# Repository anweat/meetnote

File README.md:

# MeetNote · 可挂佩的 AI 会议助手

[中文](README.md) · [English](README.en.md) · [在线主页](https://anweat.github.io/meetnote/)

> 从「桌面会议记录器」到「圆润、可挂佩的 AI 助手」：四轮产品定义、硬件架构、结构/热设计与成本研究。

**状态：工程概念研究 · `BLOCKED / NOT FOR FAB`。**
本项目交付的是可编辑、可复核的设计研究资料，**不可投板、不可采购、不可作为量产或性能承诺**。所有功耗、续航、温度、成本均为设计估算，尚无实物测试（E2 = 0）。

## 这是什么

MeetNote 是一个「随手记录 → 本地可靠保存 → 服务器理解 → 有证据的回顾」的便携 AI 助手概念。设备以胸前挂佩为主要形态，拍照时摘下取景，多人会议时放到桌面。它要减少的是「掏手机、开应用、事后翻找」这三步，而不是再做一个录音笔。

项目不追求一次性画出成品，而是按 **R0 → R1 → R2 → R3** 四轮推进：每轮给出可编辑的工程文件、明确的计算口径、验证结果和**未关闭风险**，再决定下一轮是否值得继续。

**核心设计原则**

1. **知情同意与物理许可**：上电默认不采集；独立实体开关切断麦克风/相机许可，状态灯由真实采集轨驱动，软件只是补充。
2. **本地先可靠保存**：断网不影响录制；只有本地原子落盘成功才向用户显示「已保存」。
3. **有证据的候选，而非自动执行**：摘要、待办、决定只标为候选，必须能回溯到原始音频区间/照片，并经用户确认。
4. **先证明再承诺**：FPGA 是否保留、43 °C 触温、2 小时续航、300 元成本，都设了明确的实测门槛，未通过就不写进结论。
5. **研究等级透明**：所有结论标注 E0（设计估算）/ E1（本机工具验证）/ E2（实物测试），本轮 E2 为零。

## 四轮迭代一览

| 轮次 | 定位 | 关键产出 | 结论 |
|---|---|---|---|
| [R0](iterations/MeetNote-R0/) | 桌面 4–8 人会议记录器 | KiCad 四层载板草案（主图 + 7 子页）、FreeCAD 外壳、BOM、OpenAPI 草案、12 项本机软件测试、8 页原理图 PDF | 建立了可编辑基线；ERC 3 错 7 警、DRC 4 违规 + 93 未连接，**不可投板** |
| [R1](iterations/MeetNote-R1-design/) | 可挂佩 AI 助手（定位转向） | 产品与工程基线、离线交互原型 `design-review.html`、热/续航/成本敏感性计算 | 形态与交互成立度提升；68×90×26 mm 热筛查 FAIL（估算壳温约 62.8 °C） |
| [R2](iterations/MeetNote-R2-metal/) | 金属壳、贴合与运动/定位 | 60 个最终对象的 FreeCAD 装配、STEP/STL、Blender 场景与 5 张渲染、单台成本模型 | 空间包络可行，但整机估算 155–190 g、单台 1985–4530 元，**不适合作为轻巧挂坠定型** |
| [R3 Lite](iterations/MeetNote-Lite-R3/) | 200–300 元低成本路线 | 选型与预算、架构对比、增配清单、验证顺序 | 接近 300 元的自装实验机有条件成立；**200 元完整实现没有可信采购闭环** |

## 当前设计快照

| 维度 | 现状（研究值） |
|---|---|
| 形态 | 胸前挂佩 / 手持拍照 / 桌面会议三姿态 |
| 尺寸演进 | 82×118×29 mm（R0 台架）→ 68×90×26 mm（R1 目标）→ 76×104×34 mm（R2 金属样机，含挂点总高约 108 mm） |
| 质量 | 120–160 g（R0 估算）→ 65–95 g（R1 目标）→ 155–190 g（R2 金属样机估算） |
| 续航 | 2.39 h（R0）/ 2.25 h（R1 会议 + 间歇点屏）/ 2.09 h（R2 含 GNSS、IMU）@ 2500 mAh，均为估算 |
| 主方案 | Raspberry Pi Zero 2 W + iCE40UP5K + 4×IM69D130 PDM 麦 + Camera Module 3 AF |
| 低成本方案 | Luckfox Pico Mini A（RV1103）+ Tang Nano 1K + SC3336 + 双麦 + USB Wi-Fi |
| 成本 | 100 台 500 元/台分配目标；单台金属样机 1985–4530 元；Lite 目标 296 元（区间 245–403） |
| 软件 | 加密分片、断点续传、幂等重试、人工确认参考实现；OpenAPI 草案；**未部署、无固件** |
| 验证等级 | 以 E1 本机验证为主（KiCad/FreeCAD/Blender/Python 测试），E2 实物测试为零 |

## 仓库结构

```text
.
├── README.md                     # 本文件：项目总览与导航
├── README.en.md                  # English overview
├── docs/                         # 跨轮次整理后的产品设计文档（建议从这里读）
│   ├── 00-产品设计总览.md          # 定位、用户、形态、闭环、决策与指标
│   ├── 01-需求与交互.md            # R01–R11 基线、MVP 三动作、状态与反馈
│   ├── 02-系统架构与软件协议.md     # 数据通路、接口预算、功耗模型、加密与 API
│   ├── 03-机械结构与热设计.md       # 尺寸、装配、金属壳、贴合、热路径
│   ├── 04-成本与供应链.md          # 500 元分配、单台 1985–4530、Lite 296 元
│   ├── 05-风险与验证计划.md        # 风险登记、阶段门禁、下一步实测
│   └── 06-迭代记录.md             # R0–R3 的输入、产出、结论与遗留
├── iterations/                   # 四轮原始交付包（保持原样，含各自 README、清单与验证记录）
│   ├── MeetNote-R0/
│   ├── MeetNote-R1-design/
│   ├── MeetNote-R2-metal/
│   └── MeetNote-Lite-R3/
├── site/                         # GitHub Pages 静态站点（首页 + 三个交互审阅页）
├── .github/workflows/pages.yml   # Pages 自动部署
├── LICENSE                       # MIT（脚本与软件）
└── LICENSE-CC-BY-4.0             # CC BY 4.0（文档、图片、结构与工程资料）
```

每轮原始目录内的 `README.md`、`FILE_MANIFEST.csv`、`verification/` 均保留原样，是这份整理的证据来源。

## 从哪里开始读

- **只想了解产品**：[产品设计总览](docs/00-产品设计总览.md) → [迭代记录](docs/06-迭代记录.md)
- **关心怎么验证**：[风险与验证计划](docs/05-风险与验证计划.md) → R0 的 [验收记录](iterations/MeetNote-R0/verification/验收记录.md)
- **关心硬件**：[系统架构](docs/02-系统架构与软件协议.md) → [R0 ECAD 约束](iterations/MeetNote-R0/docs/03_ECAD_constraints.md)
- **关心结构与外观**：[机械与热设计](docs/03-机械结构与热设计.md) → R2 的 [设计说明与验证边界](iterations/MeetNote-R2-metal/docs/设计说明与验证边界.md)
- **关心成本**：[成本与供应链](docs/04-成本与供应链.md)

## 在线页面与交互研究

**项目主页**：[anweat.github.io/meetnote](https://anweat.github.io/meetnote/) — 产品总览、四轮迭代、关键数字与文档导航。

三个可以直接交互的研究页（纯静态，不联网、不录音、不调用 AI）：

- **R1 交互原型**：[在线打开](https://anweat.github.io/meetnote/reviews/r1.html) · [本地文件](iterations/MeetNote-R1-design/design-review.html) — 切换「记住 / 看一下 / 回顾 / 会议 / 断网」模式，切换 68×90×26 与 54×72×22 两档尺寸，调整电池与负载重算续航；键盘可操作。
- **R2 结构审阅页**：[在线打开](https://anweat.github.io/meetnote/reviews/r2.html) · [本地文件](iterations/MeetNote-R2-metal/review.html) — 金属壳、贴合、爆炸图与单台成本口径。
- **R3 Lite 审阅页**：[在线打开](https://anweat.github.io/meetnote/reviews/r3.html) · [本地文件](iterations/MeetNote-Lite-R3/review.html) — 预算、架构、增配试算与验证顺序。

页面由 `site/` 目录构建，通过 GitHub Actions 部署；原始 HTML 与源文件仍保留在 `iterations/` 下。

## 复现本机计算

只依赖 Python 标准库（R0 的软件参考测试另行安装 `requirements.txt`）：

```bash
# R0：预算/带宽/存储重算，12 项软件参考测试
python3 iterations/MeetNote-R0/scripts/budget_check.py
cd iterations/MeetNote-R0/software && python3 -m unittest -v test_pipeline

# R1：预算、续航、热筛查
python3 iterations/MeetNote-R1-design/scripts/check_design.py

# R2：单台成本与功耗模型
python3 iterations/MeetNote-R2-metal/scripts/cost_model.py

# R3：预算与带宽计算 + 审阅页构建
python3 iterations/MeetNote-Lite-R3/scripts/build_review.py
```

KiCad / FreeCAD / Blender 的重建流程见各轮 README 的「重建」一节。**本仓库不包含可用的 Gerber 下单包**；`iterations/MeetNote-R0/electronics/NOT_FOR_FAB/` 中的制造导出仅用于验证导出链路，文件名、目录说明和板上丝印均标注禁止投产。

## 重要边界与免责声明

- 这不是可制造产品，也不是投资/采购依据。原理图中的 `POWER_ASSEMBLY`、`12M288_XO`、`HARD_INTERLOCK` 是接口占位；PCB 未布线；无 FPGA bitstream、无固件、无服务端实现。
- 热目标（35 °C 环境接触面 ≤ 43 °C）**未通过估算**；电池 6 W 峰值脉冲能力未取得电芯证据；两项 RF 净空冲突保留未删。
- 成本均为人民币研究预算，**未取得供应商正式报价**，不代表可达成。
- 数据协议中的加密、密钥保护、失窃防护、安全更新只有设计草案；Zero 2 W 无已验证的安全密钥存储。
- 所有「已完成」均指本机工具/脚本层面的完成，不代表实物功能、认证或量产状态。

详细证据等级与未关闭项见 [R0 验收记录](iterations/MeetNote-R0/verification/验收记录.md)；风险清单见 [风险与验证计划](docs/05-风险与验证计划.md)。

## 许可证

- 文档、图片、机械/结构设计与工程研究资料：[CC BY 4.0](LICENSE-CC-BY-4.0)
- 脚本与软件代码：[MIT](LICENSE)

引用或再发布时请保留出处与「研究估算、非量产」的边界说明。

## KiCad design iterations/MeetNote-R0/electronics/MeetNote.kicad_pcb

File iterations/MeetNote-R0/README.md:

# MeetNote R0 — 会议记录设备工程概念原型

**结论：已经建立可编辑产品基线、ECAD/MCAD原型和检查链路；还没有完成可投板的电子工程，更没有实物可用性证明。禁止使用本包制造文件下单。**

建议从 [产品基线与可行性](docs/01_产品基线与可行性.md) 开始，再看 [验收记录](verification/验收记录.md) 和 [关键器件与证据](docs/02_关键器件与证据.md)。

## 当前基线

- Linux SoC：Zero 2 W，512MB RAM、Wi-Fi/BLE、32GB microSD预算。
- 独立FPGA：iCE40UP5K，4×IM69D130同步音频、采样计数、128KiB短缓冲；FPGA收益需和专用音频ADC方案实测比较。
- Camera Module 3自动对焦+1–2×数字裁切，默认只手动拍照，不持续上传视频。
- 推荐尺寸82×118×29mm；78×110×26mm仅为条件化缩小估算，未验证。
- 2500mAh电芯、2.45W输出端平均预算，计老化/损耗/低电量保留后约2.39h；3W则不足2h。
- 35°C环境触温43°C目标尚未证明，散热与RF净空存在2项冲突。
- 自动决定/任务均保持待确认状态，附证据时间戳。

## 工程文件

|项目|入口|状态|
|---|---|---|
|产品基线、架构、预算|[01 产品基线](docs/01_产品基线与可行性.md)|设计估算，有公式/假设/验收条件|
|器件型号、数据手册、供货/价格及替代|[02 器件证据](docs/02_关键器件与证据.md)|区分核查值与估价；未核实项目不放行|
|电源/布线/EMI/回流/射频约束|[03 ECAD约束](docs/03_ECAD_constraints.md)|列出投板前阻断项|
|软件流程、错误恢复与密钥/更新方案|[04 软件协议](docs/04_软件与数据协议.md)|设计；不是已部署固件或服务器|
|装配、公差、已检出冲突和未建模项|[05 机械约束](docs/05_机械装配与制造约束.md)|包络验证，非完整装配放行|
|KiCad项目|[MeetNote.kicad_pro](electronics/MeetNote.kicad_pro)|主图+7个子页，36个原理图引用，35个PCB封装|
|KiCad原理图与PCB|[主图](electronics/MeetNote.kicad_sch)、[PCB](electronics/MeetNote.kicad_pcb)、[8页PDF](electronics/schematic.pdf)|实际网络/封装；仍未布线，电源/时钟/隐私门控占位|
|BOM|[原生导出](electronics/BOM_native.csv)、[带工程备注](electronics/BOM_engineering.csv)|不是完整整机采购放行BOM|
|制造导出|[NOT_FOR_FAB说明](electronics/NOT_FOR_FAB/READ_ME_DO_NOT_FABRICATE.txt)|Gerber、PTH/NPTH钻孔、钻孔图、贴片坐标已导出；禁止下单|
|FreeCAD源文件|[MeetNote_R0.FCStd](mechanical/MeetNote_R0.FCStd)|可编辑尺寸和布尔特征树|
|装配STEP|[整机STEP](mechanical/MeetNote_assembly.step)、[KiCad导出PCB STEP](mechanical/carrier_from_kicad.step)|PCB为真实导入；其余多为近似器件包络|
|外壳STEP/STL|[底壳STEP](mechanical/case_base.step)、[上盖STEP](mechanical/case_lid.step)、[底壳STL](mechanical/case_base.stl)、[上盖STL](mechanical/case_lid.stl)|用于结构原型检查，未作量产强度验证|
|Blender|[可编辑场景](visuals/MeetNote_R0.blend)、[四视图总览](visuals/overview.png)|机械尺寸驱动；手型仅示意|
|API草案|[OpenAPI](software/openapi.yaml)|YAML及本地引用已检查；未部署|
|软件可运行参考|[pipeline.py](software/pipeline.py)、[测试](software/test_pipeline.py)|12项本机测试通过；不含实际采集/ASR/联网驱动|
|完整清单|[FILE_MANIFEST.csv](FILE_MANIFEST.csv)|路径、大小、SHA-256|

## 重建

`scripts/build_electronics.py` 使用KiCad随附Python/pcbnew，生成符号、分层原理图、载板及清单；随后用KiCad CLI导出XML netlist并执行`scripts/sync_netlist.py`同步网络和Review字段。`scripts/export_and_check.py`记录ERC/DRC的实际退出码并导出文件。

`scripts/build_mechanical.py` 使用FreeCAD随附Python，`PYTHONPATH`指向FreeCAD Resources/lib；它读取KiCad STEP并生成FCStd、装配和STL。`scripts/finish_freecad.FCMacro`在原生FreeCAD中保存只显示最终零件的视图属性。macOS的offscreen Qt不支持所需OpenGL，因此此宏使用原生GUI运行。

`scripts/build_blender.py`由Blender后台运行，所有设备STL统一mm→m变换，创建4张图与原生.blend。`scripts/budget_check.py`重新计算预算。`scripts/release_gate.py`本版**故意返回2**，因为客观检查尚未达到放行条件；它不屏蔽任何ERC/DRC错误。

运行软件参考测试：进入software目录，使用安装了requirements.txt依赖的Python执行 `python -m unittest -v test_pipeline`。测试只在临时目录内产生数据和随机密钥，工程包不包含生产凭据。

## 下一版应首先实测的三件事

1. **电池/供电/热**：真实电芯在低电量、拍照+上传峰值和35°C环境连续2h，记录各轨电压/峰值电流/效率、壳体热点和电池温度；验证低电量封存及充电限制。通过条件包括无欠压复位、2h完成、既定触温及电芯规格内运行。
2. **音频连续性与物理停止**：4–8人真实会议，上传/拍照/SD写入并行，注入200ms主机服务停顿；对照采样计数测丢样、串音、噪声和ASR可用度。冻结软件时操作实体开关，硬件采集必须停止、指示灯准确；同时决定FPGA是否值得保留。
3. **带壳图像与无线**：装真实FPC、金属散热件和电池，对比裸板/带壳Wi-Fi有效吞吐、BLE共存及2小时断网续传；在0.5–3m距离拍白板和投影，核查原图/裁切文字可读性、AF、频闪和手抖。通过后再缩小外形。

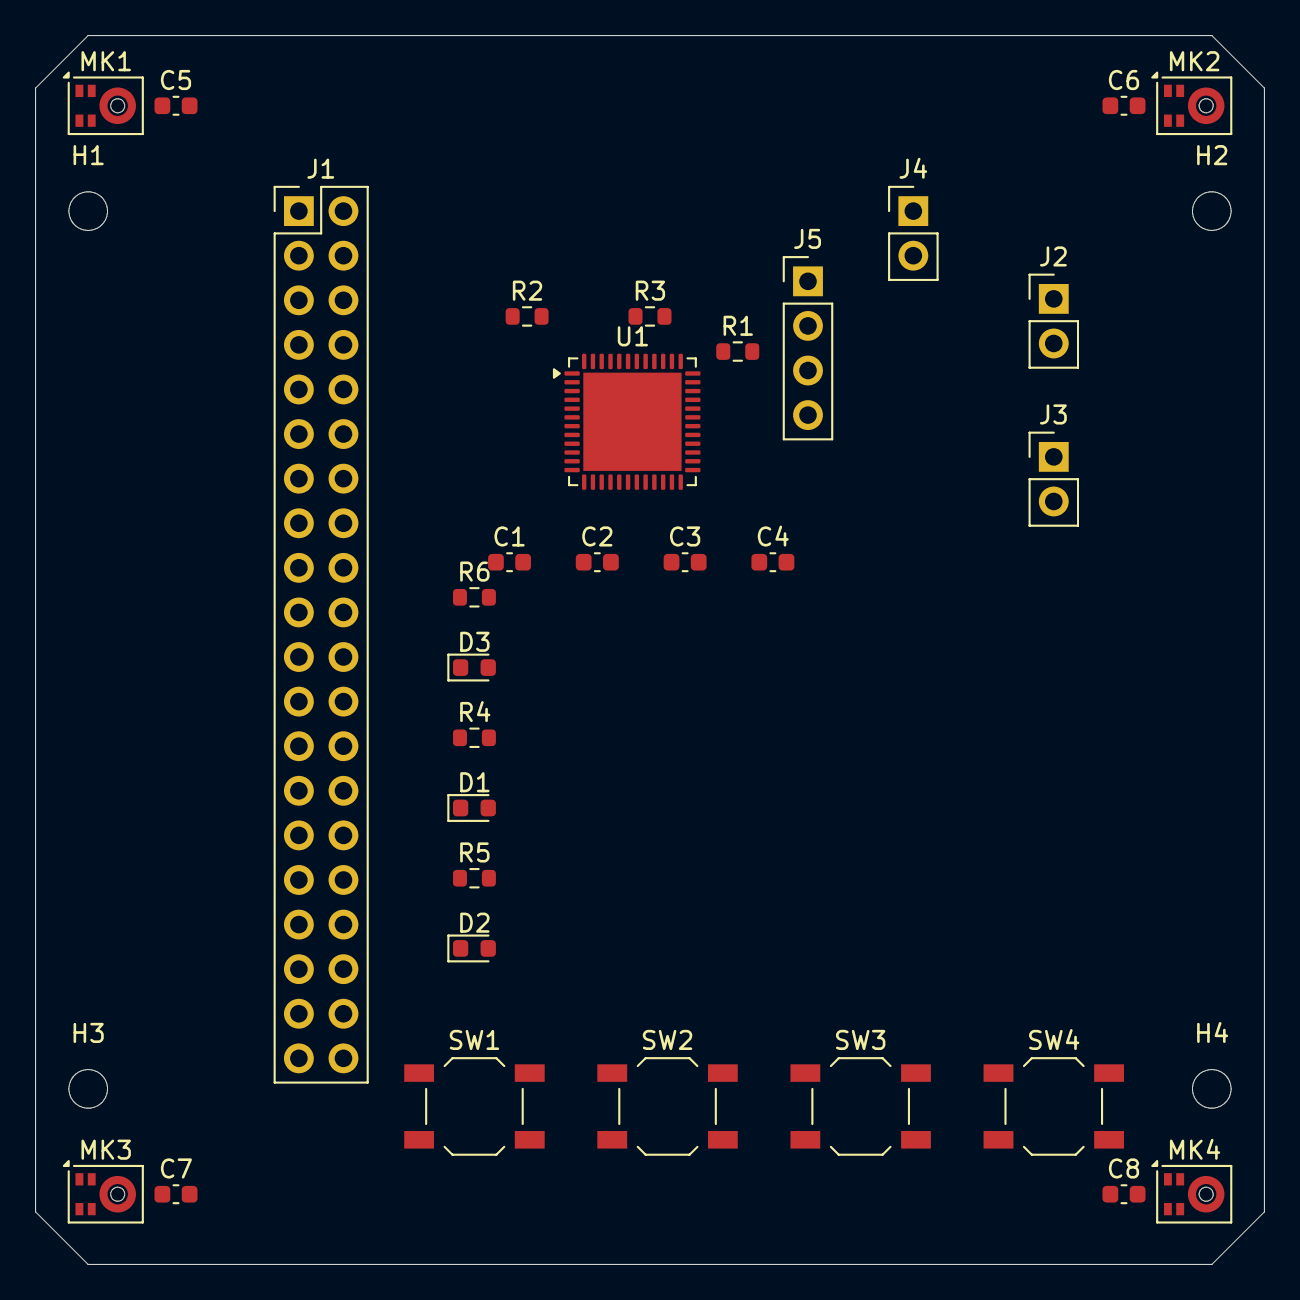
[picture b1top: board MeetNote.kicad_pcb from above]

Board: 4 copper layers, 70.0 x 70.0 mm, 35 parts (0 on the bottom side), 29 nets, no tracks yet.

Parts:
C1, C2, C3, C4, C5, C6, C7, C8: 100nF 10V; C_0603_1608Metric
D1: RED MIC POWER; LED_0603_1608Metric
D2: AMBER CAMERA POWER; LED_0603_1608Metric
D3: BLUE UPLOAD; LED_0603_1608Metric
H1, H2, H3, H4: MountingHole_2.2mm_M2
J1: Zero 2 W GPIO via short harness; PinHeader_2x20_P2.54mm_Vertical
J2: BATTERY 1S; PinHeader_1x02_P2.54mm_Vertical
J3: REGULATED 5V IN; PinHeader_1x02_P2.54mm_Vertical
J4: CELL NTC; PinHeader_1x02_P2.54mm_Vertical
J5: UART 3V3 debug; PinHeader_1x04_P2.54mm_Vertical
MK1, MK2, MK3, MK4: IM69D130; Infineon_PG-LLGA-5-1
R1: 100R PLL filter provisional; R_0603_1608Metric
R2, R3: 10k; R_0603_1608Metric
R4, R5, R6: 1k provisional; R_0603_1608Metric
SW1: REC_BUTTON; SW_SPST_TL3342
SW2: CAM_BUTTON; SW_SPST_TL3342
SW3: ZOOM_PLUS; SW_SPST_TL3342
SW4: ZOOM_MINUS; SW_SPST_TL3342
U1: ICE40UP5K-SG48ITR; QFN-48-1EP_7x7mm_P0.5mm_EP5.6x5.6mm

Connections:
CAM_BUTTON: J1.13, SW2.1
FPGA_DONE: J1.22, R3.2, U1.7
FPGA_IRQ: J1.7, U1.31
FPGA_RESET: J1.12, R2.2, U1.8
GND: C1.2, C2.2, C3.2, C4.2, C5.2, C6.2, C7.2, C8.2, D1.1, D2.1, D3.1, J1.6, J1.9, J1.14, J1.20, J1.25, J1.30, J1.34, J1.39, J2.2, J3.2, J4.2, J5.1, MK1.4, MK1.5, MK2.4, MK2.5, MK3.4, MK3.5, MK4.4, MK4.5, SW1.2, SW2.2, SW3.2, SW4.2, U1.49
LED1_A: D1.2, R4.2
LED2_A: D2.2, R5.2
LED3_A: D3.2, R6.2
MIC_CAPTURE_VDD: C5.1, C6.1, C7.1, C8.1, MK1.2, MK2.2, MK3.2, MK4.2
PDM_CLK: MK1.3, MK2.3, MK3.3, MK4.3, U1.28
PDM_D1: MK1.1, U1.23
PDM_D2: MK2.1, U1.25
PDM_D3: MK3.1, U1.26
PDM_D4: MK4.1, U1.27
REC_BUTTON: J1.11, SW1.1
SPI_CS: J1.24, U1.16
SPI_MISO: J1.21, U1.14
SPI_MOSI: J1.19, U1.17
SPI_SCK: J1.23, U1.15
SYS_5V: J1.2, J1.4, J3.1
UART_RX: J1.10, J5.3
UART_TX: J1.8, J5.2
UPLOAD_LED_CTL: J1.18, R6.1
V1V2: C1.1, R1.1, U1.5, U1.30
V1V2_PLL: C2.1, R1.2, U1.29
V2V5: C3.1, U1.24
V3V3: C4.1, J1.1, J1.17, J5.4, R2.1, R3.1, U1.1, U1.22, U1.33
ZOOM_MINUS: J1.16, SW4.1
ZOOM_PLUS: J1.15, SW3.1

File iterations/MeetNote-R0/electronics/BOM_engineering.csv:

Reference,Value,Footprint,Status,Review
U10,UNVERIFIED BQ24074 + boost + rails + gating,,DRAFT_NOT_FOR_PURCHASE,"BLOCKER: power design, USB-C CC detection, thermistor and hard gates not implemented"
J2,BATTERY 1S,Connector_PinHeader_2.54mm:PinHeader_1x02_P2.54mm_Vertical,DRAFT_NOT_FOR_PURCHASE,Provisional 2.54mm engineering header; NOT approved battery connector
J3,REGULATED 5V IN,Connector_PinHeader_2.54mm:PinHeader_1x02_P2.54mm_Vertical,DRAFT_NOT_FOR_PURCHASE,Provisional 2.54mm engineering header; NOT approved battery connector
J4,CELL NTC,Connector_PinHeader_2.54mm:PinHeader_1x02_P2.54mm_Vertical,DRAFT_NOT_FOR_PURCHASE,Provisional 2.54mm engineering header; NOT approved battery connector
J1,Zero 2 W GPIO via short harness,Connector_PinHeader_2.54mm:PinHeader_2x20_P2.54mm_Vertical,DRAFT_NOT_FOR_PURCHASE,GPIO physical numbering; harness length and final connector height TBD; not direct stacked HAT
U1,ICE40UP5K-SG48ITR,Package_DFN_QFN:QFN-48-1EP_7x7mm_P0.5mm_EP5.6x5.6mm,DRAFT_NOT_FOR_PURCHASE,Library geometry; manufacturer pin review pending
Y1,UNVERIFIED 12.288MHz XO,,DRAFT_NOT_FOR_PURCHASE,"BLOCKER: order code, jitter, supply and footprint not verified"
R1,100R PLL filter provisional,Resistor_SMD:R_0603_1608Metric,DRAFT_NOT_FOR_PURCHASE,Library geometry; manufacturer pin review pending
C1,100nF 10V,Capacitor_SMD:C_0603_1608Metric,DRAFT_NOT_FOR_PURCHASE,Library geometry; manufacturer pin review pending
C2,100nF 10V,Capacitor_SMD:C_0603_1608Metric,DRAFT_NOT_FOR_PURCHASE,Library geometry; manufacturer pin review pending
C3,100nF 10V,Capacitor_SMD:C_0603_1608Metric,DRAFT_NOT_FOR_PURCHASE,Library geometry; manufacturer pin review pending
C4,100nF 10V,Capacitor_SMD:C_0603_1608Metric,DRAFT_NOT_FOR_PURCHASE,Library geometry; manufacturer pin review pending
R2,10k,Resistor_SMD:R_0603_1608Metric,DRAFT_NOT_FOR_PURCHASE,Library geometry; manufacturer pin review pending
R3,10k,Resistor_SMD:R_0603_1608Metric,DRAFT_NOT_FOR_PURCHASE,Library geometry; manufacturer pin review pending
MK1,IM69D130,Sensor_Audio:Infineon_PG-LLGA-5-1,DRAFT_NOT_FOR_PURCHASE,Library geometry; manufacturer pin review pending
C5,100nF 10V,Capacitor_SMD:C_0603_1608Metric,DRAFT_NOT_FOR_PURCHASE,Library geometry; manufacturer pin review pending
MK2,IM69D130,Sensor_Audio:Infineon_PG-LLGA-5-1,DRAFT_NOT_FOR_PURCHASE,Library geometry; manufacturer pin review pending
C6,100nF 10V,Capacitor_SMD:C_0603_1608Metric,DRAFT_NOT_FOR_PURCHASE,Library geometry; manufacturer pin review pending
MK3,IM69D130,Sensor_Audio:Infineon_PG-LLGA-5-1,DRAFT_NOT_FOR_PURCHASE,Library geometry; manufacturer pin review pending
C7,100nF 10V,Capacitor_SMD:C_0603_1608Metric,DRAFT_NOT_FOR_PURCHASE,Library geometry; manufacturer pin review pending
MK4,IM69D130,Sensor_Audio:Infineon_PG-LLGA-5-1,DRAFT_NOT_FOR_PURCHASE,Library geometry; manufacturer pin review pending
C8,100nF 10V,Capacitor_SMD:C_0603_1608Metric,DRAFT_NOT_FOR_PURCHASE,Library geometry; manufacturer pin review pending
A2,Camera Module 3 Standard external FPC,,DRAFT_NOT_FOR_PURCHASE,External Zero CSI connection; not routed on carrier. Hard power isolation/interposer unresolved
A3,Zero 2 W onboard Wi-Fi BLE,,DRAFT_NOT_FOR_PURCHASE,Already inside Zero; no second purchased module
SW1,REC_BUTTON,Button_Switch_SMD:SW_SPST_TL3342,DRAFT_NOT_FOR_PURCHASE,Switch MPN/force/travel not supplier-verified
SW2,CAM_BUTTON,Button_Switch_SMD:SW_SPST_TL3342,DRAFT_NOT_FOR_PURCHASE,Switch MPN/force/travel not supplier-verified
SW3,ZOOM_PLUS,Button_Switch_SMD:SW_SPST_TL3342,DRAFT_NOT_FOR_PURCHASE,Switch MPN/force/travel not supplier-verified
SW4,ZOOM_MINUS,Button_Switch_SMD:SW_SPST_TL3342,DRAFT_NOT_FOR_PURCHASE,Switch MPN/force/travel not supplier-verified
D1,RED MIC POWER,LED_SMD:LED_0603_1608Metric,DRAFT_NOT_FOR_PURCHASE,"Color/current MPN TBD; REC/CAM driven by hardware sensed rail, not software"
R4,1k provisional,Resistor_SMD:R_0603_1608Metric,DRAFT_NOT_FOR_PURCHASE,Library geometry; manufacturer pin review pending
D2,AMBER CAMERA POWER,LED_SMD:LED_0603_1608Metric,DRAFT_NOT_FOR_PURCHASE,"Color/current MPN TBD; REC/CAM driven by hardware sensed rail, not software"
R5,1k provisional,Resistor_SMD:R_0603_1608Metric,DRAFT_NOT_FOR_PURCHASE,Library geometry; manufacturer pin review pending
D3,BLUE UPLOAD,LED_SMD:LED_0603_1608Metric,DRAFT_NOT_FOR_PURCHASE,"Color/current MPN TBD; REC/CAM driven by hardware sensed rail, not software"
R6,1k provisional,Resistor_SMD:R_0603_1608Metric,DRAFT_NOT_FOR_PURCHASE,Library geometry; manufacturer pin review pending
SW5,UNVERIFIED dual-pole consent switch + gates,,DRAFT_NOT_FOR_PURCHASE,BLOCKER: independent physical camera/microphone enable + anti-backfeed design incomplete
J5,UART 3V3 debug,Connector_PinHeader_2.54mm:PinHeader_1x04_P2.54mm_Vertical,DRAFT_NOT_FOR_PURCHASE,Library geometry; manufacturer pin review pending

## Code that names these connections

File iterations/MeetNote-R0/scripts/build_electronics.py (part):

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 add('power',CON2,ref,val,*xy,ns,'Connector_PinHeader_2.54mm:PinHeader_1x02_P2.54mm_Vertical',pos,note='Provisional 2.54mm engineering header; NOT approved battery connector')
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add('compute',CON,'J1','Zero 2 W GPIO via short harness',95,90,pi,'Connector_PinHeader_2.54mm:PinHeader_2x20_P2.54mm_Vertical',(15,10),note='GPIO physical numbering; harness length and final connector height TBD; not direct stacked HAT')
fpins={1:'V3V3',5:'V1V2',30:'V1V2',29:'V1V2_PLL',24:'V2V5',22:'V3V3',33:'V3V3',49:'GND',7:'FPGA_DONE',8:'FPGA_RESET',14:'SPI_MISO',15:'SPI_SCK',16:'SPI_CS',17:'SPI_MOSI',23:'PDM_D1',25:'PDM_D2',26:'PDM_D3',27:'PDM_D4',28:'PDM_CLK',31:'FPGA_IRQ',35:'AUDIO_MCLK'}
for u,x,y in [(1,65,75),(2,150,75),(3,65,160),(4,150,160)]:add('fpga',FPGA,'U1','ICE40UP5K-SG48ITR',x,y,fpins,'Package_DFN_QFN:QFN-48-1EP_7x7mm_P0.5mm_EP5.6x5.6mm',(34,22),u)
# clock source is placeholder until exact 3.3V 12.288MHz XO selected
clk=block('UNVERIFIED_12M288_XO',[('VDD','power_in'),('GND','power_in'),('OUT','output')]);add('fpga',clk,'Y1','UNVERIFIED 12.288MHz XO',235,65,{1:'V3V3',2:'GND',3:'AUDIO_MCLK'},note='BLOCKER: order code, jitter, supply and footprint not verified')
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 add('ui_debug',LED,f'D{i}',['RED MIC POWER','AMBER CAMERA POWER','BLUE UPLOAD'][i-1],60+i*48,112,{1:'GND',2:f'LED{i}_A'},'LED_SMD:LED_0603_1608Metric',pos,note='Color/current MPN TBD; REC/CAM driven by hardware sensed rail, not software')
 add('ui_debug',R,f'R{i+3}','1k provisional',60+i*48,92,{1:name,2:f'LED{i}_A'},r_fp,(pos[0],pos[1]-4))
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add('ui_debug',CON4,'J5','UART 3V3 debug',160,160,{1:'GND',2:'UART_TX',3:'UART_RX',4:'V3V3'},'Connector_PinHeader_2.54mm:PinHeader_1x04_P2.54mm_Vertical',(44,14))

# Native hierarchical schematics
names={'power':'01 POWER - UNRESOLVED','compute':'02 COMPUTE AND STORAGE','fpga':'03 FPGA AUDIO FRONT END','camera':'04 CAMERA - EXTERNAL','audio':'05 FOUR MICROPHONES','wireless':'06 WIRELESS - EMBEDDED','ui_debug':'07 UI AND DEBUG'}
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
